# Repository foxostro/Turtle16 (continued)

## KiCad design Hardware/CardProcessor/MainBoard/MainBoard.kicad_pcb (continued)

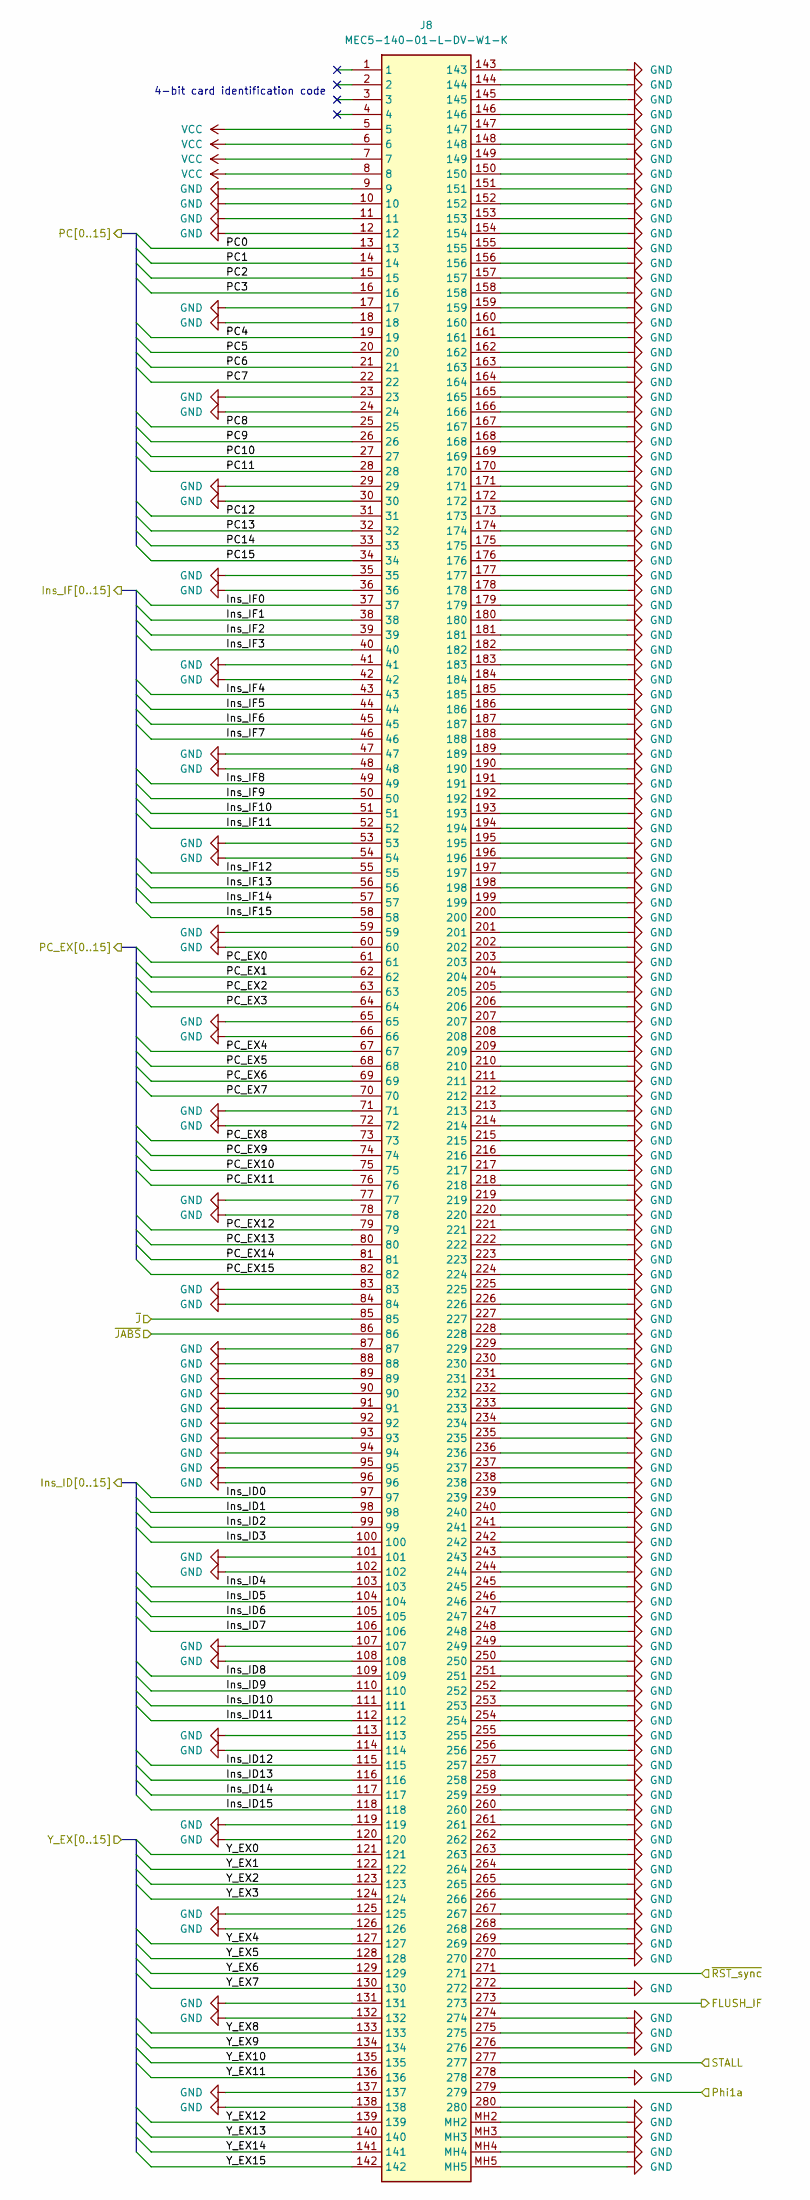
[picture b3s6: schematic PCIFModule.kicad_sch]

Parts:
J8: MEC5-140-01-L-DV-W1-K; MEC514001LDVW1K; Mouser Part Number 200-MEC514001LDVW1K

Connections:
/BypassModule/Y_EX0: J8.121; also elsewhere on the board
/BypassModule/Y_EX1: J8.122; also elsewhere on the board
/BypassModule/Y_EX2: J8.123; also elsewhere on the board
/BypassModule/Y_EX3: J8.124; also elsewhere on the board
/BypassModule/Y_EX4: J8.127; also elsewhere on the board
/BypassModule/Y_EX5: J8.128; also elsewhere on the board
/BypassModule/Y_EX6: J8.129; also elsewhere on the board
/BypassModule/Y_EX7: J8.130; also elsewhere on the board
/BypassModule/Y_EX8: J8.133; also elsewhere on the board
/BypassModule/Y_EX9: J8.134; also elsewhere on the board
/BypassModule/Y_EX10: J8.135; also elsewhere on the board
/BypassModule/Y_EX11: J8.136; also elsewhere on the board
/BypassModule/Y_EX12: J8.139; also elsewhere on the board
/BypassModule/Y_EX13: J8.140; also elsewhere on the board
/BypassModule/Y_EX14: J8.141; also elsewhere on the board
/BypassModule/Y_EX15: J8.142; also elsewhere on the board
/ControlModule/Ctl_EX12: J8.85; also elsewhere on the board
/ControlModule/Ctl_EX13: J8.86; also elsewhere on the board
/ControlModule/Ins_ID0: J8.97; also elsewhere on the board
/ControlModule/Ins_ID1: J8.98; also elsewhere on the board
/ControlModule/Ins_ID2: J8.99; also elsewhere on the board
/ControlModule/Ins_ID3: J8.100; also elsewhere on the board
/ControlModule/Ins_ID4: J8.103; also elsewhere on the board
/ControlModule/Ins_ID5: J8.104; also elsewhere on the board
/ControlModule/Ins_ID6: J8.105; also elsewhere on the board
/ControlModule/Ins_ID7: J8.106; also elsewhere on the board
/ControlModule/Ins_ID8: J8.109; also elsewhere on the board
/ControlModule/Ins_ID9: J8.110; also elsewhere on the board
/ControlModule/Ins_ID10: J8.111; also elsewhere on the board
/ControlModule/Ins_ID11: J8.112; also elsewhere on the board
/ControlModule/Ins_ID12: J8.115; also elsewhere on the board
/ControlModule/Ins_ID13: J8.116; also elsewhere on the board
/ControlModule/Ins_ID14: J8.117; also elsewhere on the board
/ControlModule/Ins_ID15: J8.118; also elsewhere on the board
/ControlModule/STALL: J8.277; also elsewhere on the board
/EXModule/PC_EX0: J8.61; also elsewhere on the board
/EXModule/PC_EX1: J8.62; also elsewhere on the board
/EXModule/PC_EX2: J8.63; also elsewhere on the board
/EXModule/PC_EX3: J8.64; also elsewhere on the board
/EXModule/PC_EX4: J8.67; also elsewhere on the board
/EXModule/PC_EX5: J8.68; also elsewhere on the board
/EXModule/PC_EX6: J8.69; also elsewhere on the board
/EXModule/PC_EX7: J8.70; also elsewhere on the board
/EXModule/PC_EX8: J8.73; also elsewhere on the board
/EXModule/PC_EX9: J8.74; also elsewhere on the board
/EXModule/PC_EX10: J8.75; also elsewhere on the board
/EXModule/PC_EX11: J8.76; also elsewhere on the board
/EXModule/PC_EX12: J8.79; also elsewhere on the board
/EXModule/PC_EX13: J8.80; also elsewhere on the board
/EXModule/PC_EX14: J8.81; also elsewhere on the board
/EXModule/PC_EX15: J8.82; also elsewhere on the board
/MEMModule/FLUSH_IF: J8.273; also elsewhere on the board
/MEMModule/Ins_IF0: J8.37; also elsewhere on the board
/MEMModule/Ins_IF1: J8.38; also elsewhere on the board
/MEMModule/Ins_IF2: J8.39; also elsewhere on the board
/MEMModule/Ins_IF3: J8.40; also elsewhere on the board
/MEMModule/Ins_IF4: J8.43; also elsewhere on the board
/MEMModule/Ins_IF5: J8.44; also elsewhere on the board
/MEMModule/Ins_IF6: J8.45; also elsewhere on the board
/MEMModule/Ins_IF7: J8.46; also elsewhere on the board
/MEMModule/Ins_IF8: J8.49; also elsewhere on the board
/MEMModule/Ins_IF9: J8.50; also elsewhere on the board
/MEMModule/Ins_IF10: J8.51; also elsewhere on the board
/MEMModule/Ins_IF11: J8.52; also elsewhere on the board
/MEMModule/Ins_IF12: J8.55; also elsewhere on the board
/MEMModule/Ins_IF13: J8.56; also elsewhere on the board
/MEMModule/Ins_IF14: J8.57; also elsewhere on the board
/MEMModule/Ins_IF15: J8.58; also elsewhere on the board
/MEMModule/PC0: J8.13; also elsewhere on the board
/MEMModule/PC1: J8.14; also elsewhere on the board
/MEMModule/PC2: J8.15; also elsewhere on the board
/MEMModule/PC3: J8.16; also elsewhere on the board
/MEMModule/PC4: J8.19; also elsewhere on the board
/MEMModule/PC5: J8.20; also elsewhere on the board
/MEMModule/PC6: J8.21; also elsewhere on the board
/MEMModule/PC7: J8.22; also elsewhere on the board
/MEMModule/PC8: J8.25; also elsewhere on the board
/MEMModule/PC9: J8.26; also elsewhere on the board
/MEMModule/PC10: J8.27; also elsewhere on the board
/MEMModule/PC11: J8.28; also elsewhere on the board
/MEMModule/PC12: J8.31; also elsewhere on the board
/MEMModule/PC13: J8.32; also elsewhere on the board
/MEMModule/PC14: J8.33; also elsewhere on the board
/MEMModule/PC15: J8.34; also elsewhere on the board
/Phi1a: J8.279; also elsewhere on the board
/~RST_sync: J8.271; also elsewhere on the board
GND: J8.9, J8.10, J8.11, J8.12, J8.17, J8.18, J8.23, J8.24, J8.29, J8.30, J8.35, J8.36, J8.41, J8.42, J8.47, J8.48, J8.53, J8.54, J8.59, J8.60, J8.65, J8.66, J8.71, J8.72, J8.77, J8.78, J8.83, J8.84, J8.87, J8.88, J8.89, J8.90, J8.91, J8.92, J8.93, J8.94, J8.95, J8.96, J8.101, J8.102, J8.107, J8.108, J8.113, J8.114, J8.119, J8.120, J8.125, J8.126, J8.131, J8.132, J8.137, J8.138, J8.143, J8.144, J8.145, J8.146, J8.147, J8.148, J8.149, J8.150, J8.151, J8.152, J8.153, J8.154, J8.155, J8.156, J8.157, J8.158, J8.159, J8.160, J8.161, J8.162, J8.163, J8.164, J8.165, J8.166, J8.167, J8.168, J8.169, J8.170, J8.171, J8.172, J8.173, J8.174, J8.175, J8.176, J8.177, J8.178, J8.179, J8.180, J8.181, J8.182, J8.183, J8.184, J8.185, J8.186, J8.187, J8.188, J8.189, J8.190, J8.191, J8.192, J8.193, J8.194, J8.195, J8.196, J8.197, J8.198, J8.199, J8.200, J8.201, J8.202, J8.203, J8.204, J8.205, J8.206, J8.207, J8.208, J8.209, J8.210, J8.211, J8.212, J8.213, J8.214, J8.215, J8.216, J8.217, J8.218, J8.219, J8.220, J8.221, J8.222, J8.223, J8.224, J8.225, J8.226, J8.227, J8.228, J8.229, J8.230, J8.231, J8.232, J8.233, J8.234, J8.235, J8.236, J8.237, J8.238, J8.239, J8.240, J8.241, J8.242, J8.243, J8.244, J8.245, J8.246, J8.247, J8.248, J8.249, J8.250, J8.251, J8.252, J8.253, J8.254, J8.255, J8.256, J8.257, J8.258, J8.259, J8.260, J8.261, J8.262, J8.263, J8.264, J8.265, J8.266, J8.267, J8.268, J8.269, J8.270, J8.272, J8.274, J8.275, J8.276, J8.278, J8.280, J8.MH2, J8.MH3, J8.MH4, J8.MH5; also elsewhere on the board
VCC: J8.5, J8.6, J8.7, J8.8; also elsewhere on the board

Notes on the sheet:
4-bit card identification code

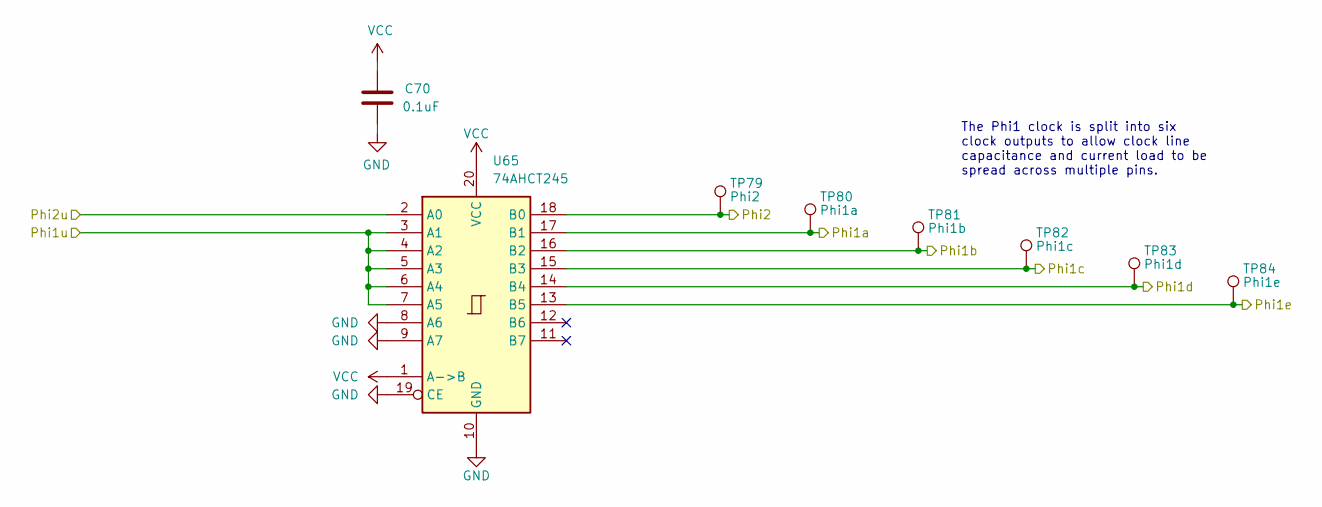
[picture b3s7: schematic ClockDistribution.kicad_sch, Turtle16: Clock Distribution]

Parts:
C70: 0.1uF; C_0603_1608Metric; Manufacturer# EMK107B7104KAHT; Mouser# 963-EMK107B7104KAHT
TP79: Phi2; TestPoint_Pad_D1.0mm
TP80: Phi1a; TestPoint_Pad_D1.0mm
TP81: Phi1b; TestPoint_Pad_D1.0mm
TP82: Phi1c; TestPoint_Pad_D1.0mm
TP83: Phi1d; TestPoint_Pad_D1.0mm
TP84: Phi1e; TestPoint_Pad_D1.0mm
U65: 74AHCT245; TSSOP-20_4.4x6.5mm_P0.65mm; Manufacturer# SN74AHCT245PWR; Mouser# 595-SN74AHCT245PWR

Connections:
/Phi1a: TP80.1, U65.17 (B1); also elsewhere on the board
/Phi1b: TP81.1, U65.16 (B2); also elsewhere on the board
/Phi1c: TP82.1, U65.15 (B3); also elsewhere on the board
/Phi1d: TP83.1, U65.14 (B4); also elsewhere on the board
/Phi1e: TP84.1, U65.13 (B5); also elsewhere on the board
/Phi1u: U65.3 (A1), U65.4 (A2), U65.5 (A3), U65.6 (A4), U65.7 (A5); also elsewhere on the board
/Phi2: TP79.1, U65.18 (B0); also elsewhere on the board
/Phi2u: U65.2 (A0); also elsewhere on the board
GND: C70.2, U65.8 (A6), U65.9 (A7), U65.10 (GND), U65.19 (CE); also elsewhere on the board
VCC: C70.1, U65.1 (A->B), U65.20 (VCC); also elsewhere on the board

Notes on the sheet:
The Phi1 clock is split into six clock outputs to allow clock line capacitance and current load to be spread across multiple pins.

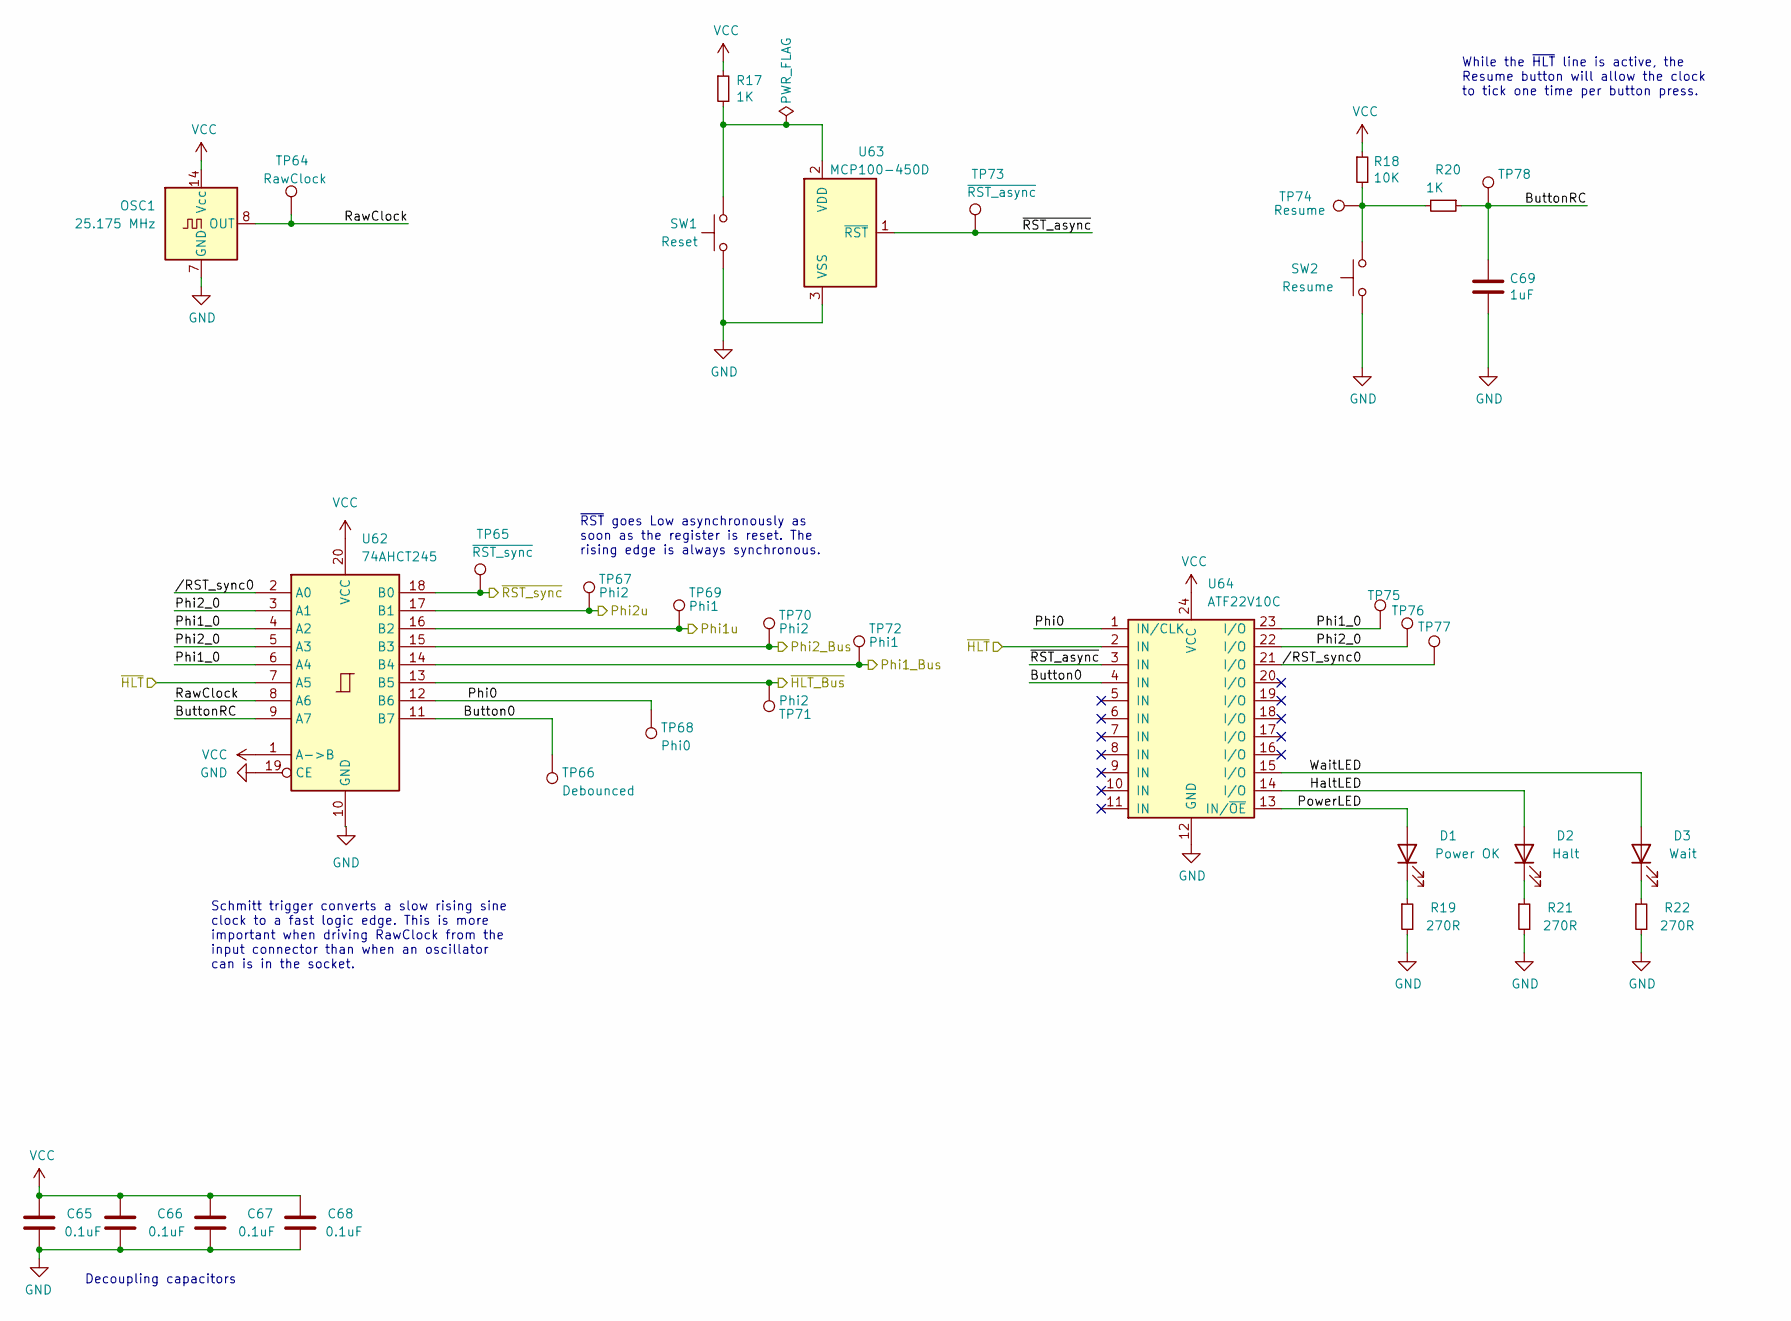
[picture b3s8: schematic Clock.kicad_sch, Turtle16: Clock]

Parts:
C65, C66, C67, C68: 0.1uF; C_0603_1608Metric; Manufacturer# EMK107B7104KAHT; Mouser# 963-EMK107B7104KAHT
C69: 1uF; C_0603_1608Metric; Manufacturer# CR0603-FX-2700ELF; Mouser# 652-CR0603FX-2700ELF
D1: Power OK; LED_0805_2012Metric; Manufacturer# AP2012ID; Mouser# 604-AP2012ID
D2: Halt; LED_0805_2012Metric; Manufacturer# AP2012ID; Mouser# 604-AP2012ID
D3: Wait; LED_0805_2012Metric; Manufacturer# AP2012ID; Mouser# 604-AP2012ID
OSC1: 25.175 MHz; Oscillator_DIP-14; Manufacturer# 1107741; Mouser# 535-1107741
R17: 1K; R_0603_1608Metric; Manufacturer# CR0603-FX-1002ELF; Mouser# 652-CR0603FX-1002ELF
R18: 10K; R_0603_1608Metric; Manufacturer# CR0603-FX-1002ELF; Mouser# 652-CR0603FX-1002ELF
R19, R21, R22: 270R; R_0603_1608Metric; Manufacturer# CR0603-FX-2700ELF; Mouser# 652-CR0603FX-2700ELF
R20: 1K; R_0603_1608Metric; Manufacturer# CR0603-FX-1001ELF; Mouser# 652-CR0603FX-1001ELF
SW1: Reset; SW_PUSH_6mm_H5mm
SW2: Resume; SW_PUSH_6mm_H5mm
TP64: RawClock; TestPoint_Pad_D1.0mm
TP65: ~{RST_sync}; TestPoint_Pad_D1.0mm
TP66: Debounced; TestPoint_Pad_D1.0mm
TP67, TP70, TP71: Phi2; TestPoint_Pad_D1.0mm
TP68: Phi0; TestPoint_Pad_D1.0mm
TP69, TP72: Phi1; TestPoint_Pad_D1.0mm
TP73: ~{RST_async}; TestPoint_Pad_D1.0mm
TP74: Resume; TestPoint_Pad_D1.0mm
TP75: TestPoint_Pad_D1.0mm
TP76, TP77, TP78: TP; TestPoint_Pad_D1.0mm
U62: 74AHCT245; TSSOP-20_4.4x6.5mm_P0.65mm; Manufacturer# SN74AHCT245PWR; Mouser# 595-SN74AHCT245PWR
U63: MCP100-450D; TO-92; Manufacturer# MCP100-450DI/TO; Mouser# 579-MCP100-450DI/TO
U64: ATF22V10C; DIP-24_W7.62mm_Socket; Manufacturer# ATF22V10C-7PX; Mouser# 556-AF22V10C7PX

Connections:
/Clock/Button0: TP66.1, U62.11 (B7), U64.4 (IN)
/Clock/ButtonRC: C69.1, R20.1, TP78.1, U62.9 (A7)
/Clock/HaltLED: D2.2 (A), U64.14 (I/O)
/Clock/Phi0: TP68.1, U62.12 (B6), U64.1 (IN/CLK)
/Clock/Phi1_0: TP75.1, U62.4 (A2), U62.6 (A4), U64.23 (I/O)
/Clock/Phi2_0: TP76.1, U62.3 (A1), U62.5 (A3), U64.22 (I/O)
/Clock/PowerLED: D1.2 (A), U64.13 (IN/~OE)
/Clock/RawClock: OSC1.8 (OUT), TP64.1, U62.8 (A6)
/Clock/WaitLED: D3.2 (A), U64.15 (I/O)
/Clock//RST_sync0: TP77.1, U62.2 (A0), U64.21 (I/O)
/Clock/~RST_async: TP73.1, U63.1 (~RST), U64.3 (IN)
/ControlModule/Ctl_EX0: U62.7 (A5), U64.2 (IN); also elsewhere on the board
/Phi1_Bus: TP72.1, U62.14 (B4); also elsewhere on the board
/Phi1u: TP69.1, U62.16 (B2); also elsewhere on the board
/Phi2_Bus: TP70.1, U62.15 (B3); also elsewhere on the board
/Phi2u: TP67.1, U62.17 (B1); also elsewhere on the board
/~HLT_Bus: TP71.1, U62.13 (B5); also elsewhere on the board
/~RST_sync: TP65.1, U62.18 (B0); also elsewhere on the board
GND: C65.2, C66.2, C67.2, C68.2, C69.2, OSC1.7 (GND), R19.2, R21.2, R22.2, SW1.1, SW2.1, U62.10 (GND), U62.19 (CE), U63.3 (VSS), U64.12 (GND); also elsewhere on the board
unnamed: D1.1 (K), R19.1
unnamed: D2.1 (K), R21.1
unnamed: D3.1 (K), R22.1
unnamed: R18.2, R20.2, SW2.2, TP74.1
unnamed: R17.2, SW1.2, U63.2 (VDD)
VCC: C65.1, C66.1, C67.1, C68.1, OSC1.14 (Vcc), R17.1, R18.1, U62.1 (A->B), U62.20 (VCC), U64.24 (VCC); also elsewhere on the board

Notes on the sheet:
~{RST} goes Low asynchronously as soon as the register is reset. The rising edge is always synchronous.
Schmitt trigger converts a slow rising sine clock to a fast logic edge. This is more important when driving RawClock from the input connector than when an oscillator can is in the socket.
While the ~{HLT} line is active, the Resume button will allow the clock to tick one time per button press.
Decoupling capacitors

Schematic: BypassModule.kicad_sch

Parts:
J5: MEC5-140-01-L-DV-W1-K; MEC514001LDVW1K; Mouser Part Number 200-MEC514001LDVW1K

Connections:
/BypassModule/A0: J5.203; also elsewhere on the board
/BypassModule/A1: J5.204; also elsewhere on the board
/BypassModule/A2: J5.205; also elsewhere on the board
/BypassModule/A3: J5.206; also elsewhere on the board
/BypassModule/A4: J5.209; also elsewhere on the board
/BypassModule/A5: J5.210; also elsewhere on the board
/BypassModule/A6: J5.211; also elsewhere on the board
/BypassModule/A7: J5.212; also elsewhere on the board
/BypassModule/A8: J5.215; also elsewhere on the board
/BypassModule/A9: J5.216; also elsewhere on the board
/BypassModule/A10: J5.217; also elsewhere on the board
/BypassModule/A11: J5.218; also elsewhere on the board
/BypassModule/A12: J5.221; also elsewhere on the board
/BypassModule/A13: J5.222; also elsewhere on the board
/BypassModule/A14: J5.223; also elsewhere on the board
/BypassModule/A15: J5.224; also elsewhere on the board
/BypassModule/B0: J5.179; also elsewhere on the board
/BypassModule/B1: J5.180; also elsewhere on the board
/BypassModule/B2: J5.181; also elsewhere on the board
/BypassModule/B3: J5.182; also elsewhere on the board
/BypassModule/B4: J5.185; also elsewhere on the board
/BypassModule/B5: J5.186; also elsewhere on the board
/BypassModule/B6: J5.187; also elsewhere on the board
/BypassModule/B7: J5.188; also elsewhere on the board
/BypassModule/B8: J5.191; also elsewhere on the board
/BypassModule/B9: J5.192; also elsewhere on the board
/BypassModule/B10: J5.193; also elsewhere on the board
/BypassModule/B11: J5.194; also elsewhere on the board
/BypassModule/B12: J5.197; also elsewhere on the board
/BypassModule/B13: J5.198; also elsewhere on the board
/BypassModule/B14: J5.199; also elsewhere on the board
/BypassModule/B15: J5.200; also elsewhere on the board
/BypassModule/FWD_A: J5.13; also elsewhere on the board
/BypassModule/FWD_B: J5.16; also elsewhere on the board
/BypassModule/FWD_EX_TO_A: J5.14; also elsewhere on the board
/BypassModule/FWD_EX_TO_B: J5.19; also elsewhere on the board
/BypassModule/FWD_MEM_TO_A: J5.15; also elsewhere on the board
/BypassModule/FWD_MEM_TO_B: J5.20; also elsewhere on the board
/BypassModule/RegisterA0: J5.73; also elsewhere on the board
/BypassModule/RegisterA1: J5.74; also elsewhere on the board
/BypassModule/RegisterA2: J5.75; also elsewhere on the board
/BypassModule/RegisterA3: J5.76; also elsewhere on the board
/BypassModule/RegisterA4: J5.79; also elsewhere on the board
/BypassModule/RegisterA5: J5.80; also elsewhere on the board
/BypassModule/RegisterA6: J5.81; also elsewhere on the board
/BypassModule/RegisterA7: J5.82; also elsewhere on the board
/BypassModule/RegisterA8: J5.85; also elsewhere on the board
/BypassModule/RegisterA9: J5.86; also elsewhere on the board
/BypassModule/RegisterA10: J5.87; also elsewhere on the board
/BypassModule/RegisterA11: J5.88; also elsewhere on the board
/BypassModule/RegisterA12: J5.91; also elsewhere on the board
/BypassModule/RegisterA13: J5.92; also elsewhere on the board
/BypassModule/RegisterA14: J5.93; also elsewhere on the board
/BypassModule/RegisterA15: J5.94; also elsewhere on the board
/BypassModule/RegisterB0: J5.227; also elsewhere on the board
/BypassModule/RegisterB1: J5.228; also elsewhere on the board
/BypassModule/RegisterB2: J5.229; also elsewhere on the board
/BypassModule/RegisterB3: J5.230; also elsewhere on the board
/BypassModule/RegisterB4: J5.233; also elsewhere on the board
/BypassModule/RegisterB5: J5.234; also elsewhere on the board
/BypassModule/RegisterB6: J5.235; also elsewhere on the board
/BypassModule/RegisterB7: J5.236; also elsewhere on the board
/BypassModule/RegisterB8: J5.239; also elsewhere on the board
/BypassModule/RegisterB9: J5.240; also elsewhere on the board
/BypassModule/RegisterB10: J5.241; also elsewhere on the board
/BypassModule/RegisterB11: J5.242; also elsewhere on the board
/BypassModule/RegisterB12: J5.245; also elsewhere on the board
/BypassModule/RegisterB13: J5.246; also elsewhere on the board
/BypassModule/RegisterB14: J5.247; also elsewhere on the board
/BypassModule/RegisterB15: J5.248; also elsewhere on the board
/BypassModule/Y_EX0: J5.121; also elsewhere on the board
/BypassModule/Y_EX1: J5.122; also elsewhere on the board
/BypassModule/Y_EX2: J5.123; also elsewhere on the board
/BypassModule/Y_EX3: J5.124; also elsewhere on the board
/BypassModule/Y_EX4: J5.127; also elsewhere on the board
/BypassModule/Y_EX5: J5.128; also elsewhere on the board
/BypassModule/Y_EX6: J5.129; also elsewhere on the board
/BypassModule/Y_EX7: J5.130; also elsewhere on the board
/BypassModule/Y_EX8: J5.133; also elsewhere on the board
/BypassModule/Y_EX9: J5.134; also elsewhere on the board
/BypassModule/Y_EX10: J5.135; also elsewhere on the board
/BypassModule/Y_EX11: J5.136; also elsewhere on the board
/BypassModule/Y_EX12: J5.139; also elsewhere on the board
/BypassModule/Y_EX13: J5.140; also elsewhere on the board
/BypassModule/Y_EX14: J5.141; also elsewhere on the board
/BypassModule/Y_EX15: J5.142; also elsewhere on the board
/BypassModule/Y_MEM0: J5.251; also elsewhere on the board
/BypassModule/Y_MEM1: J5.252; also elsewhere on the board
/BypassModule/Y_MEM2: J5.253; also elsewhere on the board
/BypassModule/Y_MEM3: J5.254; also elsewhere on the board
/BypassModule/Y_MEM4: J5.257; also elsewhere on the board
/BypassModule/Y_MEM5: J5.258; also elsewhere on the board
/BypassModule/Y_MEM6: J5.259; also elsewhere on the board
/BypassModule/Y_MEM7: J5.260; also elsewhere on the board
/BypassModule/Y_MEM8: J5.263; also elsewhere on the board
/BypassModule/Y_MEM9: J5.264; also elsewhere on the board
/BypassModule/Y_MEM10: J5.265; also elsewhere on the board
/BypassModule/Y_MEM11: J5.266; also elsewhere on the board
/BypassModule/Y_MEM12: J5.269; also elsewhere on the board
/BypassModule/Y_MEM13: J5.270; also elsewhere on the board
/BypassModule/Y_MEM14: J5.271; also elsewhere on the board
/BypassModule/Y_MEM15: J5.272; also elsewhere on the board
/Phi1d: J5.279; also elsewhere on the board
GND: J5.9, J5.10, J5.11, J5.12, J5.17, J5.18, J5.21, J5.22, J5.23, J5.24, J5.25, J5.26, J5.27, J5.28, J5.29, J5.30, J5.31, J5.32, J5.33, J5.34, J5.35, J5.36, J5.37, J5.38, J5.39, J5.40, J5.41, J5.42, J5.43, J5.44, J5.45, J5.46, J5.47, J5.48, J5.49, J5.50, J5.51, J5.52, J5.53, J5.54, J5.55, J5.56, J5.57, J5.58, J5.59, J5.60, J5.61, J5.62, J5.63, J5.64, J5.65, J5.66, J5.67, J5.68, J5.69, J5.70, J5.71, J5.72, J5.77, J5.78, J5.83, J5.84, J5.89, J5.90, J5.95, J5.96, J5.97, J5.98, J5.99, J5.100, J5.101, J5.102, J5.103, J5.104, J5.105, J5.106, J5.107, J5.108, J5.109, J5.110, J5.111, J5.112, J5.113, J5.114, J5.115, J5.116, J5.117, J5.118, J5.119, J5.120, J5.125, J5.126, J5.131, J5.132, J5.137, J5.138, J5.143, J5.144, J5.145, J5.146, J5.147, J5.148, J5.149, J5.150, J5.151, J5.152, J5.153, J5.154, J5.155, J5.156, J5.157, J5.158, J5.159, J5.160, J5.161, J5.162, J5.163, J5.164, J5.165, J5.166, J5.167, J5.168, J5.169, J5.170, J5.171, J5.172, J5.173, J5.174, J5.175, J5.176, J5.177, J5.178, J5.183, J5.184, J5.189, J5.190, J5.195, J5.196, J5.201, J5.202, J5.207, J5.208, J5.213, J5.214, J5.219, J5.220, J5.225, J5.226, J5.231, J5.232, J5.237, J5.238, J5.243, J5.244, J5.249, J5.250, J5.255, J5.256, J5.261, J5.262, J5.267, J5.268, J5.273, J5.274, J5.275, J5.276, J5.277, J5.278, J5.280, J5.MH2, J5.MH3, J5.MH4, J5.MH5; also elsewhere on the board
VCC: J5.5, J5.6, J5.7, J5.8; also elsewhere on the board

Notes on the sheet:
4-bit card identification code

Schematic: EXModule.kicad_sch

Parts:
J3: MEC5-140-01-L-DV-W1-K; MEC514001LDVW1K; Mouser Part Number 200-MEC514001LDVW1K

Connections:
/BypassModule/A0: J3.203; also elsewhere on the board
/BypassModule/A1: J3.204; also elsewhere on the board
/BypassModule/A2: J3.205; also elsewhere on the board
/BypassModule/A3: J3.206; also elsewhere on the board
/BypassModule/A4: J3.209; also elsewhere on the board
/BypassModule/A5: J3.210; also elsewhere on the board
/BypassModule/A6: J3.211; also elsewhere on the board
/BypassModule/A7: J3.212; also elsewhere on the board
/BypassModule/A8: J3.215; also elsewhere on the board
/BypassModule/A9: J3.216; also elsewhere on the board
/BypassModule/A10: J3.217; also elsewhere on the board
/BypassModule/A11: J3.218; also elsewhere on the board
/BypassModule/A12: J3.221; also elsewhere on the board
/BypassModule/A13: J3.222; also elsewhere on the board
/BypassModule/A14: J3.223; also elsewhere on the board
/BypassModule/A15: J3.224; also elsewhere on the board
/BypassModule/B0: J3.179; also elsewhere on the board
/BypassModule/B1: J3.180; also elsewhere on the board
/BypassModule/B2: J3.181; also elsewhere on the board
/BypassModule/B3: J3.182; also elsewhere on the board
/BypassModule/B4: J3.185; also elsewhere on the board
/BypassModule/B5: J3.186; also elsewhere on the board
/BypassModule/B6: J3.187; also elsewhere on the board
/BypassModule/B7: J3.188; also elsewhere on the board
/BypassModule/B8: J3.191; also elsewhere on the board
/BypassModule/B9: J3.192; also elsewhere on the board
/BypassModule/B10: J3.193; also elsewhere on the board
/BypassModule/B11: J3.194; also elsewhere on the board
/BypassModule/B12: J3.197; also elsewhere on the board
/BypassModule/B13: J3.198; also elsewhere on the board
/BypassModule/B14: J3.199; also elsewhere on the board
/BypassModule/B15: J3.200; also elsewhere on the board
/BypassModule/Y_EX0: J3.121; also elsewhere on the board
/BypassModule/Y_EX1: J3.122; also elsewhere on the board
/BypassModule/Y_EX2: J3.123; also elsewhere on the board
/BypassModule/Y_EX3: J3.124; also elsewhere on the board
/BypassModule/Y_EX4: J3.127; also elsewhere on the board
/BypassModule/Y_EX5: J3.128; also elsewhere on the board
/BypassModule/Y_EX6: J3.129; also elsewhere on the board
/BypassModule/Y_EX7: J3.130; also elsewhere on the board
/BypassModule/Y_EX8: J3.133; also elsewhere on the board
/BypassModule/Y_EX9: J3.134; also elsewhere on the board
/BypassModule/Y_EX10: J3.135; also elsewhere on the board
/BypassModule/Y_EX11: J3.136; also elsewhere on the board
/BypassModule/Y_EX12: J3.139; also elsewhere on the board
/BypassModule/Y_EX13: J3.140; also elsewhere on the board
/BypassModule/Y_EX14: J3.141; also elsewhere on the board
/BypassModule/Y_EX15: J3.142; also elsewhere on the board
/BypassModule/Y_MEM0: J3.251; also elsewhere on the board
/BypassModule/Y_MEM1: J3.252; also elsewhere on the board
/BypassModule/Y_MEM2: J3.253; also elsewhere on the board
/BypassModule/Y_MEM3: J3.254; also elsewhere on the board
/BypassModule/Y_MEM4: J3.257; also elsewhere on the board
/BypassModule/Y_MEM5: J3.258; also elsewhere on the board
/BypassModule/Y_MEM6: J3.259; also elsewhere on the board
/BypassModule/Y_MEM7: J3.260; also elsewhere on the board
/BypassModule/Y_MEM8: J3.263; also elsewhere on the board
/BypassModule/Y_MEM9: J3.264; also elsewhere on the board
/BypassModule/Y_MEM10: J3.265; also elsewhere on the board
/BypassModule/Y_MEM11: J3.266; also elsewhere on the board
/BypassModule/Y_MEM12: J3.269; also elsewhere on the board
/BypassModule/Y_MEM13: J3.270; also elsewhere on the board
/BypassModule/Y_MEM14: J3.271; also elsewhere on the board
/BypassModule/Y_MEM15: J3.272; also elsewhere on the board
/ControlModule/Carry: J3.10; also elsewhere on the board
/ControlModule/Ctl_EX0: J3.74; also elsewhere on the board
/ControlModule/Ctl_EX1: J3.75; also elsewhere on the board
/ControlModule/Ctl_EX2: J3.76; also elsewhere on the board
/ControlModule/Ctl_EX3: J3.77; also elsewhere on the board
/ControlModule/Ctl_EX4: J3.80; also elsewhere on the board
/ControlModule/Ctl_EX5: J3.81; also elsewhere on the board
/ControlModule/Ctl_EX6: J3.82; also elsewhere on the board
/ControlModule/Ctl_EX7: J3.83; also elsewhere on the board
/ControlModule/Ctl_EX8: J3.86; also elsewhere on the board
/ControlModule/Ctl_EX9: J3.87; also elsewhere on the board
/ControlModule/Ctl_EX10: J3.88; also elsewhere on the board
/ControlModule/Ctl_EX11: J3.89; also elsewhere on the board
/ControlModule/Ctl_EX12: J3.92; also elsewhere on the board
/ControlModule/Ctl_EX13: J3.93; also elsewhere on the board
/ControlModule/Ctl_EX14: J3.94; also elsewhere on the board
/ControlModule/Ctl_EX15: J3.95; also elsewhere on the board
/ControlModule/Ctl_EX16: J3.98; also elsewhere on the board
/ControlModule/Ctl_EX17: J3.99; also elsewhere on the board
/ControlModule/Ctl_EX18: J3.100; also elsewhere on the board
/ControlModule/Ctl_EX19: J3.101; also elsewhere on the board
/ControlModule/Ctl_EX20: J3.104; also elsewhere on the board
/ControlModule/Ctl_MEM14: J3.16; also elsewhere on the board
/ControlModule/Ctl_MEM15: J3.17; also elsewhere on the board
/ControlModule/Ctl_MEM16: J3.18; also elsewhere on the board
/ControlModule/Ctl_MEM17: J3.19; also elsewhere on the board
/ControlModule/Ctl_MEM18: J3.22; also elsewhere on the board
/ControlModule/Ctl_MEM19: J3.23; also elsewhere on the board
/ControlModule/Ctl_MEM20: J3.24; also elsewhere on the board
/ControlModule/Ins_EX0: J3.33; also elsewhere on the board
/ControlModule/Ins_EX1: J3.34; also elsewhere on the board
/ControlModule/Ins_EX2: J3.37; also elsewhere on the board
/ControlModule/Ins_EX3: J3.38; also elsewhere on the board
/ControlModule/Ins_EX4: J3.39; also elsewhere on the board
/ControlModule/Ins_EX5: J3.40; also elsewhere on the board
/ControlModule/Ins_EX6: J3.43; also elsewhere on the board
/ControlModule/Ins_EX7: J3.44; also elsewhere on the board
/ControlModule/Ins_EX8: J3.45; also elsewhere on the board
/ControlModule/Ins_EX9: J3.46; also elsewhere on the board
/ControlModule/Ins_EX10: J3.49; also elsewhere on the board
/ControlModule/N: J3.13; also elsewhere on the board
/ControlModule/OVF: J3.12; also elsewhere on the board
/ControlModule/SelC_MEM0: J3.27; also elsewhere on the board
/ControlModule/SelC_MEM1: J3.28; also elsewhere on the board
/ControlModule/SelC_MEM2: J3.29; also elsewhere on the board
/ControlModule/Z: J3.11; also elsewhere on the board
/EXModule/PC_EX0: J3.50; also elsewhere on the board
/EXModule/PC_EX1: J3.51; also elsewhere on the board
/EXModule/PC_EX2: J3.52; also elsewhere on the board
/EXModule/PC_EX3: J3.53; also elsewhere on the board
/EXModule/PC_EX4: J3.56; also elsewhere on the board
/EXModule/PC_EX5: J3.57; also elsewhere on the board
/EXModule/PC_EX6: J3.58; also elsewhere on the board
/EXModule/PC_EX7: J3.59; also elsewhere on the board
/EXModule/PC_EX8: J3.62; also elsewhere on the board
/EXModule/PC_EX9: J3.63; also elsewhere on the board
/EXModule/PC_EX10: J3.64; also elsewhere on the board
/EXModule/PC_EX11: J3.65; also elsewhere on the board
/EXModule/PC_EX12: J3.68; also elsewhere on the board
/EXModule/PC_EX13: J3.69; also elsewhere on the board
/EXModule/PC_EX14: J3.70; also elsewhere on the board
/EXModule/PC_EX15: J3.71; also elsewhere on the board
/EXModule/StoreOp_MEM0: J3.227; also elsewhere on the board
/EXModule/StoreOp_MEM1: J3.228; also elsewhere on the board
/EXModule/StoreOp_MEM2: J3.229; also elsewhere on the board
/EXModule/StoreOp_MEM3: J3.230; also elsewhere on the board
/EXModule/StoreOp_MEM4: J3.233; also elsewhere on the board
/EXModule/StoreOp_MEM5: J3.234; also elsewhere on the board
/EXModule/StoreOp_MEM6: J3.235; also elsewhere on the board
/EXModule/StoreOp_MEM7: J3.236; also elsewhere on the board
/EXModule/StoreOp_MEM8: J3.239; also elsewhere on the board
/EXModule/StoreOp_MEM9: J3.240; also elsewhere on the board
/EXModule/StoreOp_MEM10: J3.241; also elsewhere on the board
/EXModule/StoreOp_MEM11: J3.242; also elsewhere on the board
/EXModule/StoreOp_MEM12: J3.245; also elsewhere on the board
/EXModule/StoreOp_MEM13: J3.246; also elsewhere on the board
/EXModule/StoreOp_MEM14: J3.247; also elsewhere on the board
/EXModule/StoreOp_MEM15: J3.248; also elsewhere on the board
/Phi1e: J3.279; also elsewhere on the board
GND: J3.9, J3.14, J3.15, J3.20, J3.21, J3.25, J3.26, J3.30, J3.31, J3.32, J3.35, J3.36, J3.41, J3.42, J3.47, J3.48, J3.54, J3.55, J3.60, J3.61, J3.66, J3.67, J3.72, J3.73, J3.78, J3.79, J3.84, J3.85, J3.90, J3.91, J3.96, J3.97, J3.102, J3.103, J3.105, J3.106, J3.107, J3.108, J3.109, J3.110, J3.111, J3.112, J3.113, J3.114, J3.115, J3.116, J3.117, J3.118, J3.119, J3.120, J3.125, J3.126, J3.131, J3.132, J3.137, J3.138, J3.143, J3.144, J3.145, J3.146, J3.147, J3.148, J3.149, J3.150, J3.151, J3.152, J3.153, J3.154, J3.155, J3.156, J3.157, J3.158, J3.159, J3.160, J3.161, J3.162, J3.163, J3.164, J3.165, J3.166, J3.167, J3.168, J3.169, J3.170, J3.171, J3.172, J3.173, J3.174, J3.175, J3.176, J3.177, J3.178, J3.183, J3.184, J3.189, J3.190, J3.195, J3.196, J3.201, J3.202, J3.207, J3.208, J3.213, J3.214, J3.219, J3.220, J3.225, J3.226, J3.231, J3.232, J3.237, J3.238, J3.243, J3.244, J3.249, J3.250, J3.255, J3.256, J3.261, J3.262, J3.267, J3.268, J3.273, J3.274, J3.275, J3.276, J3.277, J3.278, J3.280, J3.MH2, J3.MH3, J3.MH4, J3.MH5; also elsewhere on the board
VCC: J3.5, J3.6, J3.7, J3.8; also elsewhere on the board

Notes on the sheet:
4-bit card identification code

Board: 8 copper layers, 134 parts (0 on the bottom side), 336 nets, no tracks yet.

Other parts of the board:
J9, J10: MEC5-140-01-L-DV-W1-K; MEC514001LDVW1K

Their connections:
/Addr0: J9.173, J10.173; also elsewhere on the board
/Addr1: J9.174, J10.174; also elsewhere on the board
/Addr2: J9.175, J10.175; also elsewhere on the board
/Addr3: J9.176, J10.176; also elsewhere on the board
/Addr4: J9.179, J10.179; also elsewhere on the board
/Addr5: J9.180, J10.180; also elsewhere on the board
/Addr6: J9.181, J10.181; also elsewhere on the board
/Addr7: J9.182, J10.182; also elsewhere on the board
/Addr8: J9.185, J10.185; also elsewhere on the board
/Addr9: J9.186, J10.186; also elsewhere on the board
/Addr10: J9.187, J10.187; also elsewhere on the board
/Addr11: J9.188, J10.188; also elsewhere on the board
/Addr12: J9.191, J10.191; also elsewhere on the board
/Addr13: J9.192, J10.192; also elsewhere on the board
/Addr14: J9.193, J10.193; also elsewhere on the board
/Addr15: J9.194, J10.194; also elsewhere on the board
/Bank0: J9.109, J10.109; also elsewhere on the board
/Bank1: J9.110, J10.110; also elsewhere on the board
/Bank2: J9.111, J10.111; also elsewhere on the board
/IO0: J9.197, J10.197; also elsewhere on the board
/IO1: J9.198, J10.198; also elsewhere on the board
/IO2: J9.199, J10.199; also elsewhere on the board
/IO3: J9.200, J10.200; also elsewhere on the board
/IO4: J9.203, J10.203; also elsewhere on the board
/IO5: J9.204, J10.204; also elsewhere on the board
/IO6: J9.205, J10.205; also elsewhere on the board
/IO7: J9.206, J10.206; also elsewhere on the board
/IO8: J9.209, J10.209; also elsewhere on the board
/IO9: J9.210, J10.210; also elsewhere on the board
/IO10: J9.211, J10.211; also elsewhere on the board
/IO11: J9.212, J10.212; also elsewhere on the board
/IO12: J9.215, J10.215; also elsewhere on the board
/IO13: J9.216, J10.216; also elsewhere on the board
/IO14: J9.217, J10.217; also elsewhere on the board
/IO15: J9.218, J10.218; also elsewhere on the board
/Phi1_Bus: J9.279, J10.279; also elsewhere on the board
/Phi2_Bus: J9.278, J10.278; also elsewhere on the board
/~HLT_Bus: J9.16, J10.16; also elsewhere on the board
/~MemLoad: J9.101, J10.101; also elsewhere on the board
/~MemStore: J9.102, J10.102; also elsewhere on the board
/~RST_sync: J9.276, J10.276; also elsewhere on the board
GND: J9.9, J9.10, J9.11, J9.12, J9.13, J9.14, J9.15, J9.17, J9.18, J9.19, J9.20, J9.21, J9.22, J9.23, J9.24, J9.25, J9.26, J9.27, J9.28, J9.29, J9.30, J9.31, J9.32, J9.33, J9.34, J9.35, J9.36, J9.37, J9.38, J9.39, J9.40, J9.41, J9.42, J9.43, J9.44, J9.45, J9.46, J9.47, J9.48, J9.49, J9.50, J9.51, J9.52, J9.53, J9.54, J9.55, J9.56, J9.57, J9.58, J9.59, J9.60, J9.61, J9.62, J9.63, J9.64, J9.65, J9.66, J9.67, J9.68, J9.69, J9.70, J9.71, J9.72, J9.73, J9.74, J9.75, J9.76, J9.77, J9.78, J9.79, J9.80, J9.81, J9.82, J9.83, J9.84, J9.85, J9.86, J9.87, J9.88, J9.89, J9.90, J9.91, J9.92, J9.93, J9.94, J9.95, J9.96, J9.97, J9.98, J9.99, J9.100, J9.103, J9.104, J9.105, J9.106, J9.107, J9.108, J9.112, J9.113, J9.114, J9.115, J9.116, J9.117, J9.118, J9.119, J9.120, J9.121, J9.122, J9.123, J9.124, J9.125, J9.126, J9.127, J9.128, J9.129, J9.130, J9.131, J9.132, J9.133, J9.134, J9.135, J9.136, J9.137, J9.138, J9.139, J9.140, J9.141, J9.142, J9.143, J9.144, J9.145, J9.146, J9.151, J9.152, J9.153, J9.154, J9.155, J9.156, J9.157, J9.158, J9.159, J9.160, J9.161, J9.162, J9.163, J9.164, J9.165, J9.166, J9.167, J9.168, J9.169, J9.170, J9.171, J9.172, J9.177, J9.178, J9.183, J9.184, J9.189, J9.190, J9.195, J9.196, J9.201, J9.202, J9.207, J9.208, J9.213, J9.214, J9.219, J9.220, J9.221, J9.222, J9.223, J9.224, J9.225, J9.226, J9.227, J9.228, J9.229, J9.230, J9.231, J9.232, J9.233, J9.234, J9.235, J9.236, J9.237, J9.238, J9.239, J9.240, J9.241, J9.242, J9.243, J9.244, J9.245, J9.246, J9.247, J9.248, J9.249, J9.250, J9.251, J9.252, J9.253, J9.254, J9.255, J9.256, J9.257, J9.258, J9.259, J9.260, J9.261, J9.262, J9.263, J9.264, J9.265, J9.266, J9.267, J9.268, J9.269, J9.270, J9.271, J9.272, J9.273, J9.274, J9.275, J9.277, J9.280, J9.MH2, J9.MH3, J9.MH4, J9.MH5, J10.9, J10.10, J10.11, J10.12, J10.13, J10.14, J10.15, J10.17, J10.18, J10.19, J10.20, J10.21, J10.22, J10.23, J10.24, J10.25, J10.26, J10.27, J10.28, J10.29, J10.30, J10.31, J10.32, J10.33, J10.34, J10.35, J10.36, J10.37, J10.38, J10.39, J10.40, J10.41, J10.42, J10.43, J10.44, J10.45, J10.46, J10.47, J10.48, J10.49, J10.50, J10.51, J10.52, J10.53, J10.54, J10.55, J10.56, J10.57, J10.58, J10.59, J10.60, J10.61, J10.62, J10.63, J10.64, J10.65, J10.66, J10.67, J10.68, J10.69, J10.70, J10.71, J10.72, J10.73, J10.74, J10.75, J10.76, J10.77, J10.78, J10.79, J10.80, J10.81, J10.82, J10.83, J10.84, J10.85, J10.86, J10.87, J10.88, J10.89, J10.90, J10.91, J10.92, J10.93, J10.94, J10.95, J10.96, J10.97, J10.98, J10.99, J10.100, J10.103, J10.104, J10.105, J10.106, J10.107, J10.108, J10.112, J10.113, J10.114, J10.115, J10.116, J10.117, J10.118, J10.119, J10.120, J10.121, J10.122, J10.123, J10.124, J10.125, J10.126, J10.127, J10.128, J10.129, J10.130, J10.131, J10.132, J10.133, J10.134, J10.135, J10.136, J10.137, J10.138, J10.139, J10.140, J10.141, J10.142, J10.143, J10.144, J10.145, J10.146, J10.151, J10.152, J10.153, J10.154, J10.155, J10.156, J10.157, J10.158, J10.159, J10.160, J10.161, J10.162, J10.163, J10.164, J10.165, J10.166, J10.167, J10.168, J10.169, J10.170, J10.171, J10.172, J10.177, J10.178, J10.183, J10.184, J10.189, J10.190, J10.195, J10.196, J10.201, J10.202, J10.207, J10.208, J10.213, J10.214, J10.219, J10.220, J10.221, J10.222, J10.223, J10.224, J10.225, J10.226, J10.227, J10.228, J10.229, J10.230, J10.231, J10.232, J10.233, J10.234, J10.235, J10.236, J10.237, J10.238, J10.239, J10.240, J10.241, J10.242, J10.243, J10.244, J10.245, J10.246, J10.247, J10.248, J10.249, J10.250, J10.251, J10.252, J10.253, J10.254, J10.255, J10.256, J10.257, J10.258, J10.259, J10.260, J10.261, J10.262, J10.263, J10.264, J10.265, J10.266, J10.267, J10.268, J10.269, J10.270, J10.271, J10.272, J10.273, J10.274, J10.275, J10.277, J10.280, J10.MH2, J10.MH3, J10.MH4, J10.MH5; also elsewhere on the board
VCC: J9.5, J9.6, J9.7, J9.8, J9.147, J9.148, J9.149, J9.150, J10.5, J10.6, J10.7, J10.8, J10.147, J10.148, J10.149, J10.150; also elsewhere on the board
